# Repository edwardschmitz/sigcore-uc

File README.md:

# SigCore UC – Universal Controller

**Status:**    In Development  
**Version:**   revA (prototype phase)  
**Runs on:**   Raspberry Pi OS (64-bit) with a .NET 8-based server and a C#/WPF Control Panel for Windows.

SigCore UC is a modular, high-precision universal I/O controller designed for engineers, developers, and integrators working in automation, control systems, and experimentation.

It supports a broad range of analog, digital, and current-loop signals, and is built to be both powerful and transparent—from PCB to Python.

---

## Key Features

- **Analog Inputs**
  - Millivolt to 10V input range
  - 4–20 mA loop support
  - Configurable filtering and calibration
- **Digital Inputs**
  - Logic level support from 3V to 30V
  - Built-in protection and detection
- **Relay Outputs**
  - High-current mechanical and solid-state options
  - Default-state configuration and software override
- **Analog Outputs**
  - Voltage and PWM output modes
- **Communication**
  - Ethernet 
  - Modbus and Web API integration
- **Extensibility**
  - Python and C# libraries
  - Firmware auto-update

---

## License

[MIT License](LICENSE) — open for inspection, modification, and contribution.

---

## About This Repo

SigCore UC is the successor to the [D88A42 Prototype](https://github.com/edwardschmitz/D88A42-Prototype).  
It brings forward lessons learned and raises the ceiling for custom I/O control systems.

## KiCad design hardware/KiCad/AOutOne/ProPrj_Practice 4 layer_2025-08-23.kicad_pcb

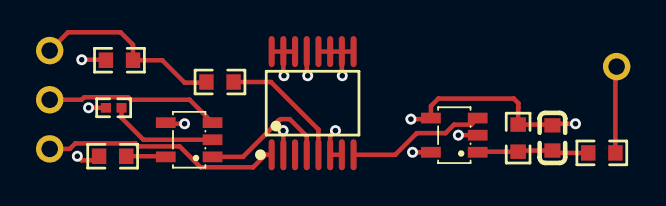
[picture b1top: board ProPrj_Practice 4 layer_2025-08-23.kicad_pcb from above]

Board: 4 copper layers, 10 parts (0 on the bottom side), 9 nets.

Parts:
C1: C0603
R1, R3, R4, R5, R6: R0603
R2: R0402
U2, U6: SOT-23-5_L3.0-W1.7-P0.95-LS2.8-BR
U5: TSSOP-16_L5.0-W4.4-P0.65-LS6.4-BL

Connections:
+5V: R1.1, U5.13, U6.5
GND: C1.2, R2.2, R4.2, R6.1, U2.4, U5.2, U5.6, U5.7, U5.9, U5.10, U5.11, U5.12, U5.14, U5.15, U5.16, U6.2, U6.4
T_DOUT-PWM: R3.1, R6.2
T_U2V+: R1.2, U2.5
T_U2V-: R2.1, U2.2
T_U5D: U5.8, U6.3
T_U5S1: U2.1, U5.4
T_U5S2: R3.2, U5.5
T_U6OUT: C1.1, R4.1, R5.1, U6.1

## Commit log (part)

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2025-12-04 Initial clean commit
2025-12-24 Minor housekeeping
2025-12-25 Remove marketing and accounting files
2026-01-15 Current State
2026-03-09 interim version
